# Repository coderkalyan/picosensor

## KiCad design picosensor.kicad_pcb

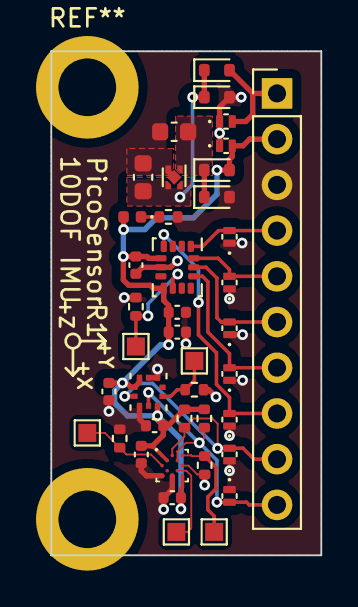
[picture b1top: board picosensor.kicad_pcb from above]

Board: 2 copper layers, 15.0 x 28.0 mm, 40 parts (0 on the bottom side), 18 nets.

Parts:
C1: 2u2; C_0402_1005Metric
C2, C6, C7, C8, C9: 0u1; C_0402_1005Metric
C3: 10n; C_0402_1005Metric
C4, C5: 0u1; C_0603_1608Metric
D1, D12: BZX58550-B5V6; D_SOD-523
D2, D11: 1PS79SB30; D_SOD-523
D3: GREEN; LED_0402_1005Metric
D4, D5, D6, D7, D8, D9, D10, D13, D14: D_TVS; DFN1006-2
J1: Conn_01x10; PinHeader_1x10_P2.54mm_Vertical
R1, R2, R5: 1K5; R_0402_1005Metric
R3, R4, R6, R7: 10K; R_0402_1005Metric
TP1: BMM150_B1; TestPoint_Pad_1.0x1.0mm
TP2: BMM150_B0; TestPoint_Pad_1.0x1.0mm
TP3: BMM150_DRDY; TestPoint_Pad_1.0x1.0mm
TP4: ICP20100_CSB; TestPoint_Pad_1.0x1.0mm
TP5: ICM42688P_FSYNC; TestPoint_Pad_1.0x1.0mm
U1: ICM42688P; LGA-14_3x2.5mm_P0.5mm_LayoutBorder3x4y
U2: TLV71333PDQN; Texas_X2SON-4_1x1mm_P0.65mm
U3: BMM150; WLCSP-12_1.56x1.56mm_P0.4mm
U4: ICP20100; PQFN50P200X200X85-10N

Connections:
+3V3: C1.2, C2.2, C3.1, C6.2, C7.1, C8.2, C9.1, D3.2 (A), D11.2 (A), D14.2 (A2), J1.2, R1.1, R2.1, U1.5 (VDDIO), U1.8 (VDD), U3.A1 (PS), U3.B2 (VDDIO), U3.E5 (VDD), U4.1 (CSB), U4.5 (VDD), U4.10 (VDDIO)
+5V: D2.2 (A), D13.2 (A2), J1.1
/BMM150_CSB: R3.1, TP2.1, U3.C1 (SDO)
/BMM150_DRDY: TP3.1, U3.D4 (DRDY)
/DRDY_ICM42688P: D6.2 (A2), J1.8, U1.4 (INT)
/MISO: D10.2 (A2), J1.4, U1.1 (AD0/SDO)
/MOSI: D9.2 (A2), J1.5, U1.14 (SDA/SDI)
/SCK: D8.2 (A2), J1.6, U1.13 (SCL/SCLK)
/SCL: D5.2 (A2), J1.9, R1.2, U3.A3 (SCK), U4.2 (SCL/SCLK)
/SDA: D4.2 (A2), J1.10, R2.2, U3.B4 (SDI), U4.4 (SDA/SDI)
/nCS: D7.2 (A2), J1.7, U1.12 (nCS)
GND: C1.1, C2.1, C3.2, C4.2, C5.2, C6.1, C7.2, C8.1, C9.2, D1.2 (A), D4.1 (A1), D5.1 (A1), D6.1 (A1), D7.1 (A1), D8.1 (A1), D9.1 (A1), D10.1 (A1), D12.2 (A), D13.1 (A1), D14.1 (A1), J1.3, R3.2, R4.2, R5.2, R6.2, R7.2, U1.6 (GND), U2.2 (GND), U2.5 (GND), U3.C5 (GND), U3.E1 (GND), U3.E3 (GND), U4.3 (VSS), U4.8 (RESV), U4.9 (RESV)
unnamed: C4.1, D1.1 (K), D2.1 (K), U2.3 (EN), U2.4 (IN)
unnamed: D3.1 (K), R5.1
unnamed: C5.1, D11.1 (K), D12.1 (K), U2.1 (OUT)
unnamed: R7.1, TP5.1, U1.9 (FSYNC)
unnamed: R4.1, TP1.1, U3.A5 (CSB)
unnamed: R6.1, TP4.1, U4.6 (AD0/SDO)
